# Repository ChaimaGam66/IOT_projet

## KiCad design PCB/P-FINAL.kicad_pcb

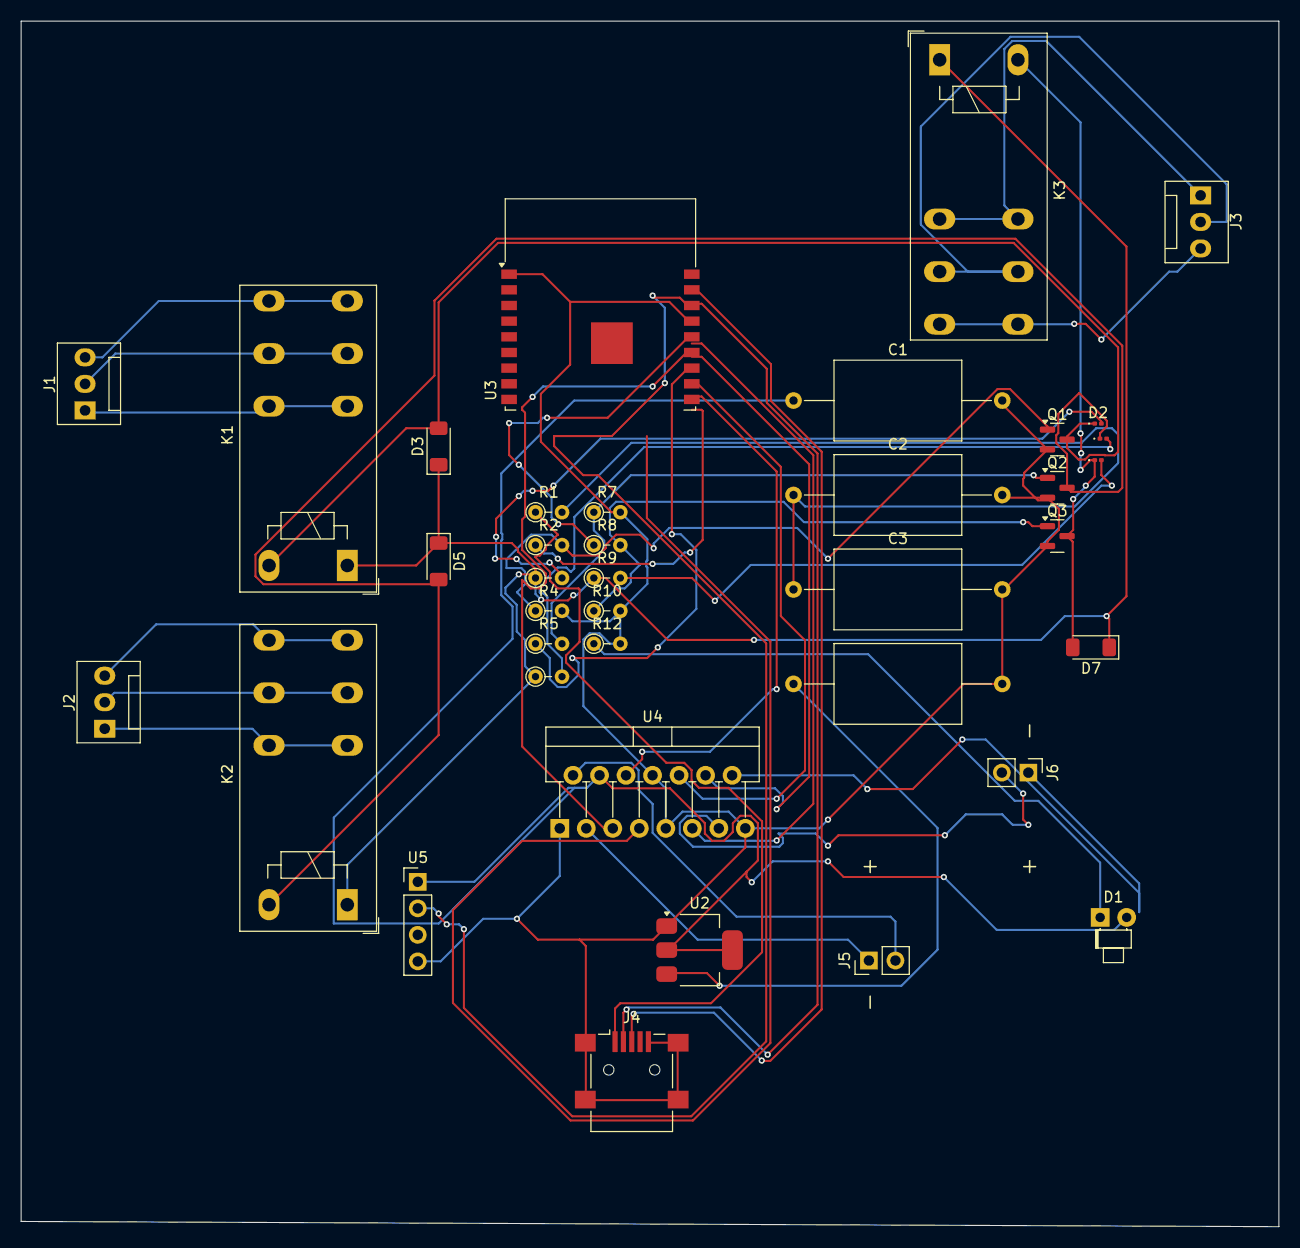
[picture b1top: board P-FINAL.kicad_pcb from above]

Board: 2 copper layers, 120.5 x 115.5 mm, 38 parts (0 on the bottom side), 32 nets.

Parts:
C1, C2, C3, C4: C; C_Axial_L12.0mm_D7.5mm_P20.00mm_Horizontal
D1: LED; LED_D1.8mm_W1.8mm_H2.4mm_Horizontal_O1.27mm_Z1.6mm
D2, D4, D6: LED; LED_0201_0603Metric
D3, D5, D7: LL4148; D_MiniMELF
J1, J2, J3: Screw_Terminal_01x03; FanPinHeader_1x03_P2.54mm_Vertical
J4: USB_B_Mini; USB_Mini-B_Lumberg_2486_01_Horizontal
J5, J6: Conn_01x02_Pin; PinHeader_1x02_P2.54mm_Vertical
K1, K2, K3: RT314A03; Relay_SPDT_Schrack-RT1-16A-FormC_RM5mm
Q1, Q2, Q3: BC817; SOT-23
R1, R2, R3, R4, R5, R6, R7, R8, R9, R10, R12: R; R_Axial_DIN0204_L3.6mm_D1.6mm_P2.54mm_Vertical
U2: AMS1117-3.3; SOT-223-3_TabPin2
U3: ESP-WROOM-02
U4: L298N; TO-220-15_P2.54x2.54mm_StaggerOdd_Lead4.58mm_Vertical
U5: DHT11; PinHeader_1x04_P2.54mm_Vertical

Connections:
+3.3V: C1.1, D1.2 (A), U2.2 (VO), U4.4 (Vs), U5.1 (VDD)
+5V: D3.1 (K), D5.1 (K), D7.1 (K), K1.A1, K2.A1, K3.A1, R3.1, R6.1, R9.1
/A: U3.16 (IO13), U5.2 (DATA)
/B: U3.13 (IO14), U4.5 (IN1)
/RELAY3: R8.1, U3.14 (IO12)
GND: C1.2, C2.2, C3.2, C4.2, J4.5 (GND), J4.6 (Shield), Q1.2 (E), Q2.2 (E), Q3.2 (E), R4.2, R7.2, R10.2, R12.2, U2.1 (GND), U3.1 (GND), U3.15 (GND), U4.1 (SENSE_A), U4.8 (GND), U4.9 (Vss), U4.15 (SENSE_B), U5.4 (GND)
unnamed: C2.1, C3.1, R1.2
unnamed: D1.1 (K), R12.1
unnamed: D2.2 (A), R3.2
unnamed: D2.1 (K), D3.2 (A), K1.A2, Q1.3 (C)
unnamed: D4.2 (A), R6.2
unnamed: D4.1 (K), D5.2 (A), K2.A2, Q2.3 (C)
unnamed: D6.2 (A), R9.2
unnamed: D6.1 (K), D7.2 (A), K3.A2, Q3.3 (C)
unnamed: J1.1, K1.12
unnamed: J1.2, K1.11
unnamed: J1.3, K1.14
unnamed: J2.1, K2.12
unnamed: J2.2, K2.11
unnamed: J2.3, K2.14
unnamed: J3.1, K3.12
unnamed: J3.2, K3.11
unnamed: J3.3, K3.14
unnamed: J4.1 (VBUS), R1.1
unnamed: J5.1, U4.3 (OUT2)
unnamed: J5.2, U4.2 (OUT1)
unnamed: J6.1, U4.14 (OUT4)
unnamed: J6.2, U4.13 (OUT3)
unnamed: Q1.1 (B), R2.2, R4.1
unnamed: Q2.1 (B), R5.2, R7.1
unnamed: Q3.1 (B), R8.2, R10.1
VBUS: C4.1, U2.3 (VI)
